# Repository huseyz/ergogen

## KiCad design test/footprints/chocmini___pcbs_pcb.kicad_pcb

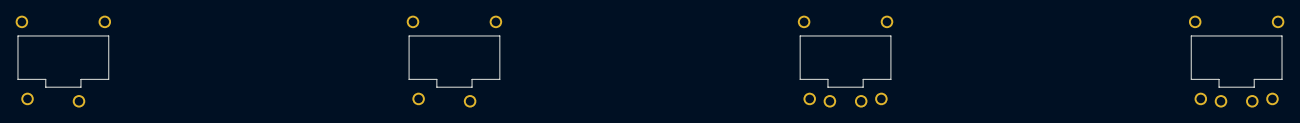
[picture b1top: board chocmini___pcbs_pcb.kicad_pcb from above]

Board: 2 copper layers, 4 parts (0 on the bottom side), 2 nets, no tracks yet.

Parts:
S1, S2, S3, S4: Kailh_PG1232

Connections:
from: S1.1, S2.1, S3.1, S4.1
to: S1.2, S2.2, S3.2, S4.2

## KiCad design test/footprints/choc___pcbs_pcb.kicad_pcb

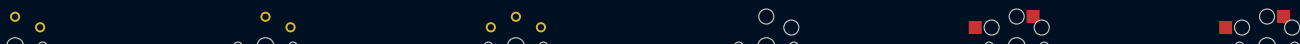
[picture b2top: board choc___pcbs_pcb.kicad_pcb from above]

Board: 2 copper layers, 6 parts (0 on the bottom side), 2 nets, no tracks yet.

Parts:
S1, S2, S3, S4, S5, S6: PG1350

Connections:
from: S1.1, S2.1, S3.1, S4.1, S5.1, S6.1
to: S1.2, S2.2, S3.2, S4.2, S5.2, S6.2

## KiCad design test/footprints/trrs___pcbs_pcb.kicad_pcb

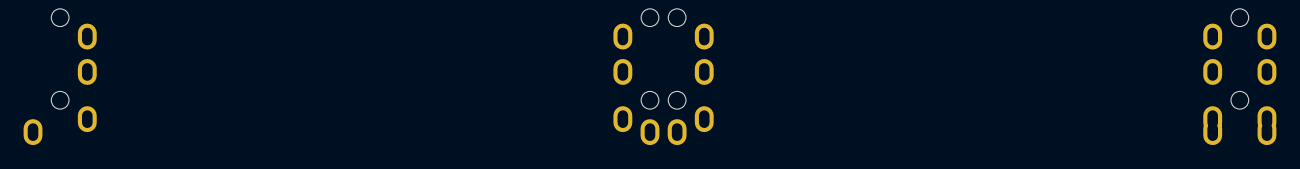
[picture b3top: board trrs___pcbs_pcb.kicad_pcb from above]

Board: 2 copper layers, 3 parts (0 on the bottom side), 4 nets, no tracks yet.

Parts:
TRRS1, TRRS2, TRRS3: TRRS-PJ-320A-dual

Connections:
A: TRRS1.1, TRRS2.1, TRRS3.1
B: TRRS1.2, TRRS2.2, TRRS3.2
C: TRRS1.3, TRRS2.3, TRRS3.3
D: TRRS1.4, TRRS2.4, TRRS3.4

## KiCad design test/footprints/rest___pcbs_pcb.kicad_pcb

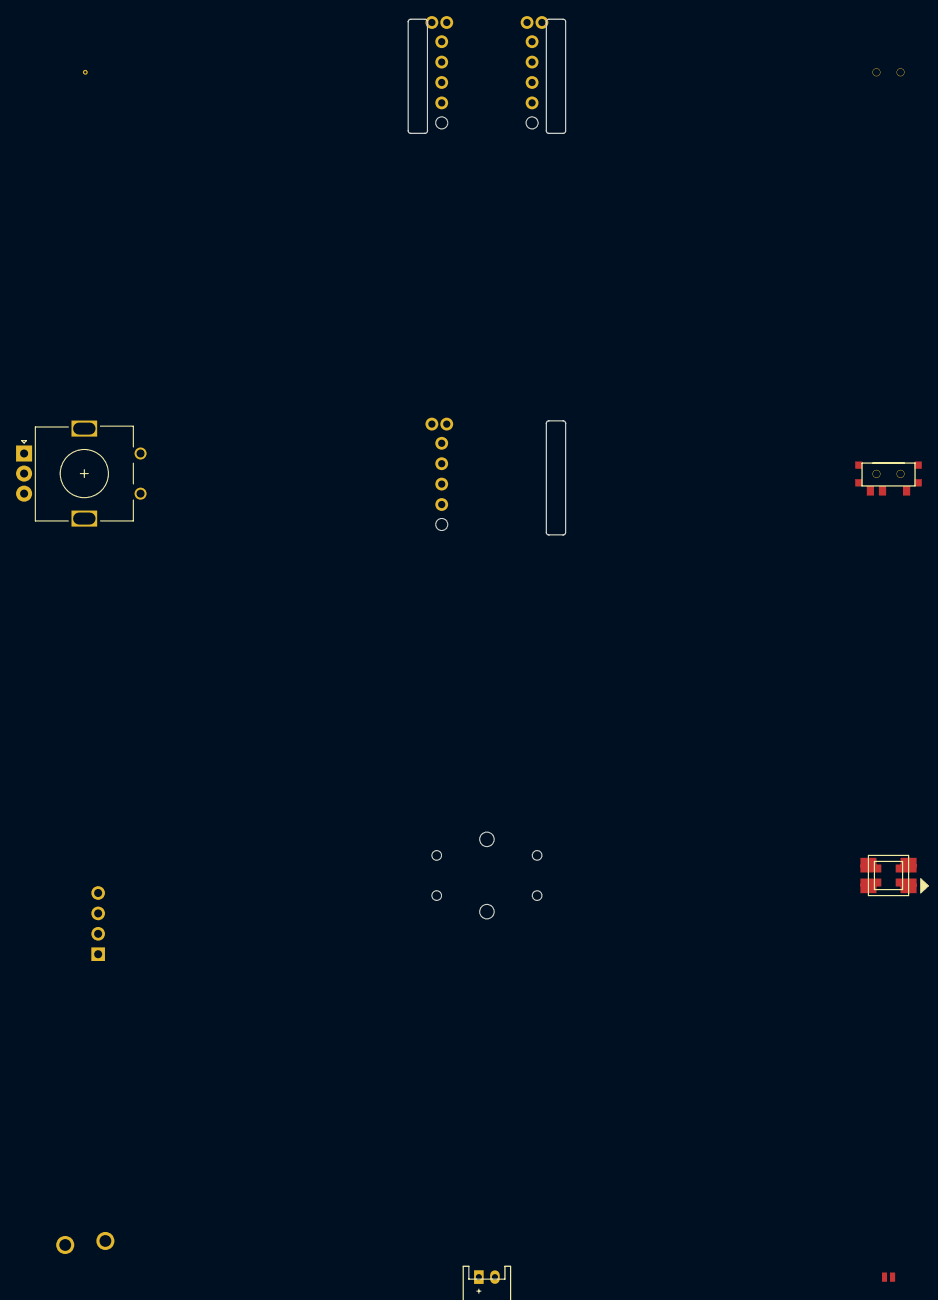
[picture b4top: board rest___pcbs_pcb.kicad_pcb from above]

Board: 2 copper layers, 9 parts (0 on the bottom side), 6 nets, no tracks yet.

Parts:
J1: Jumper
JST1: JST_PH_S2B-PH-K_02x2.00mm_Angled
LED1: WS2812B
OLED1: OLED; OLED_headers
ROT1: rotary_encoder
S1: ALPS
S2: OMRON_B3F-4055
T1, T2: SPDT_C128955

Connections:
GND: LED1.3, LED1.33, OLED1.1
VCC: LED1.1, LED1.11, OLED1.2
din: LED1.4, LED1.44
dout: LED1.2, LED1.22
from: J1.1, ROT1.1, S1.1, S2.1, S2.2, T1.1, T2.1
to: J1.2, ROT1.2, S1.2, S2.3, S2.4, T1.2, T2.2

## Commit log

2025-07-14 Improvements for ergogen-web
